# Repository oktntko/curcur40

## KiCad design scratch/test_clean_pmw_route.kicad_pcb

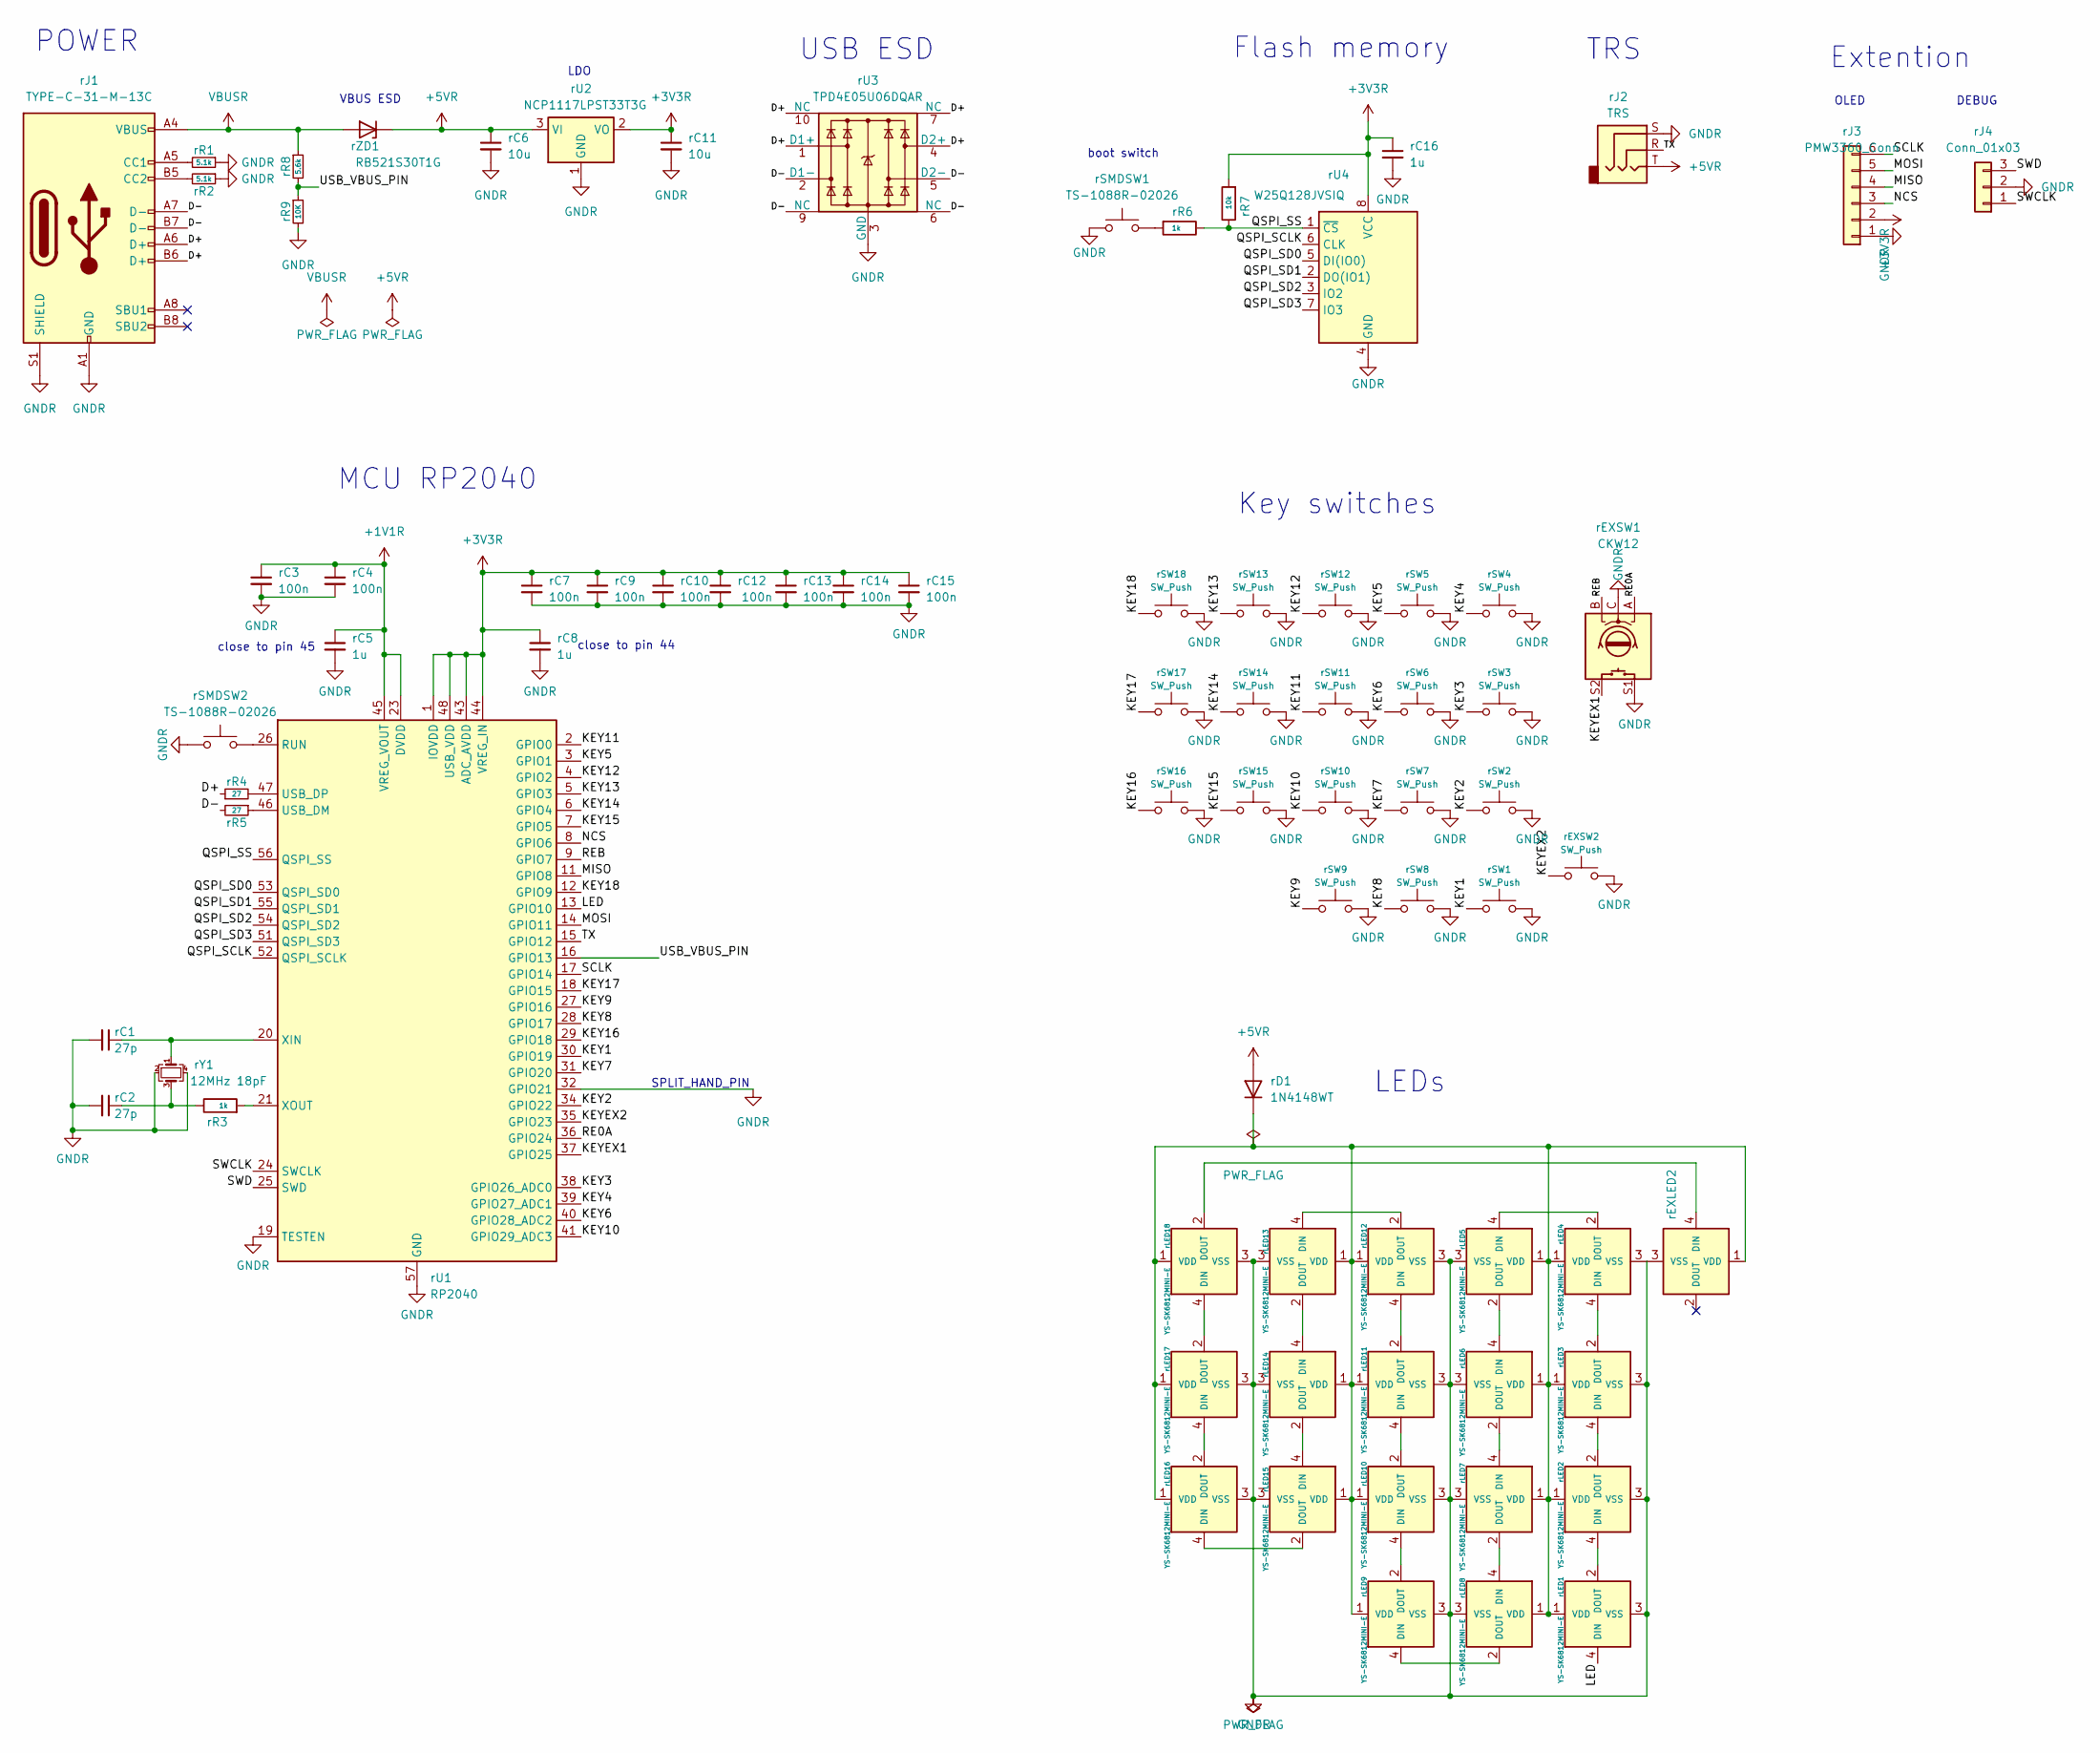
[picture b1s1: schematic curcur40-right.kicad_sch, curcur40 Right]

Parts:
rC1, rC2: 27p; C_0402_1005Metric
rC3, rC4, rC7, rC9, rC10, rC12, rC13, rC14, rC15: 100n; C_0402_1005Metric
rC5, rC8, rC16: 1u; C_0402_1005Metric
rC6, rC11: 10u; C_0402_1005Metric
rD1: 1N4148WT; D_SOD-523; JLCPCB Part # C232841
rEXLED2: YS-SK6812MINI-E
rEXSW1: CKW12
rEXSW2: SW_Push; keyswitch_choc12_hotswap_1u
rJ1: TYPE-C-31-M-13C; JLCPCB Part # C2848620
rJ2: TRS; PJ-398A-5A_PJ-399B-6A; JLCPCB Part # C128994
rJ3: PMW3360_Conn; PinHeader_1x06_P2.54mm_Vertical
rJ4: Conn_01x03; PinHeader_1x03_P2.54mm_Vertical
rLED1, rLED2, rLED3, rLED4, rLED5, rLED6, rLED7, rLED8, rLED9, rLED10, rLED11, rLED12, rLED13, rLED14, rLED15, rLED16, rLED17, rLED18: YS-SK6812MINI-E
rR1, rR2: 5.1k; R_0402_1005Metric
rR3, rR6: 1k; R_0402_1005Metric
rR4, rR5: 27; R_0402_1005Metric
rR7: 10k; R_0402_1005Metric
rR8: 5.6k; R_0402_1005Metric
rR9: 10K; R_0402_1005Metric
rSMDSW1, rSMDSW2: TS-1088R-02026; JLCPCB Part # C455280
rSW1, rSW2, rSW3, rSW4, rSW5, rSW6, rSW7, rSW8, rSW9, rSW10, rSW11, rSW12, rSW13, rSW14, rSW15, rSW16, rSW17, rSW18: SW_Push; keyswitch_choc12_hotswap_1u
rU1: RP2040; QFN-56-1EP_7x7mm_P0.4mm_EP3.2x3.2mm; JLCPCB Part # C2040
rU2: NCP1117LPST33T3G; SOT-223-3_TabPin2; JLCPCB Part # C146799
rU3: TPD4E05U06DQAR; USON-10_2.5x1.0mm_P0.5mm; JLCPCB Part # C138714
rU4: W25Q128JVSIQ; SOIC-8_5.3x5.3mm_P1.27mm; JLCPCB Part # C113767
rY1: 12MHz 18pF; Crystal_SMD_3225-4Pin_3.2x2.5mm; MFR.Part # Q22FA23V0041800; JLCPCB Part # C91749
rZD1: RB521S30T1G; D_SOD-523; JLCPCB Part # C145179

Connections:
+1V1R: rC3.1, rC4.1, rC5.1, rU1.23 (DVDD), rU1.45 (VREG_VOUT), rU1.50 (DVDD)
+3V3R: rC7.1, rC8.1, rC9.1, rC10.1, rC11.1, rC12.1, rC13.1, rC14.1, rC15.1, rC16.1, rJ3.2, rR7.2, rU1.1 (IOVDD), rU1.10 (IOVDD), rU1.22 (IOVDD), rU1.33 (IOVDD), rU1.42 (IOVDD), rU1.43 (ADC_AVDD), rU1.44 (VREG_IN), rU1.48 (USB_VDD), rU1.49 (IOVDD), rU2.2 (VO), rU4.8 (VCC); also elsewhere on the board
+5VR: rC6.1, rD1.2 (A), rJ2.T, rU2.3 (VI), rZD1.1 (K)
/D+: rJ1.A6 (D+), rJ1.B6 (D+), rR4.1, rU3.1 (D1+), rU3.4 (D2+), rU3.7 (NC), rU3.10 (NC)
/D-: rJ1.A7 (D-), rJ1.B7 (D-), rR5.2, rU3.2 (D1-), rU3.5 (D2-), rU3.6 (NC), rU3.9 (NC)
/KEY1: rSW1.1, rU1.30 (GPIO19)
/KEY2: rSW2.1, rU1.34 (GPIO22)
/KEY3: rSW3.1, rU1.38 (GPIO26_ADC0)
/KEY4: rSW4.1, rU1.39 (GPIO27_ADC1)
/KEY5: rSW5.1, rU1.3 (GPIO1)
/KEY6: rSW6.1, rU1.40 (GPIO28_ADC2)
/KEY7: rSW7.1, rU1.31 (GPIO20)
/KEY8: rSW8.1, rU1.28 (GPIO17)
/KEY9: rSW9.1, rU1.27 (GPIO16)
/KEY10: rSW10.1, rU1.41 (GPIO29_ADC3)
/KEY11: rSW11.1, rU1.2 (GPIO0)
/KEY12: rSW12.1, rU1.4 (GPIO2)
/KEY13: rSW13.1, rU1.5 (GPIO3)
/KEY14: rSW14.1, rU1.6 (GPIO4)
/KEY15: rSW15.1, rU1.7 (GPIO5)
/KEY16: rSW16.1, rU1.29 (GPIO18)
/KEY17: rSW17.1, rU1.18 (GPIO15)
/KEY18: rSW18.1, rU1.12 (GPIO9)
/KEYEX1: rEXSW1.S2, rU1.37 (GPIO25)
/KEYEX2: rEXSW2.1, rU1.35 (GPIO23)
/LED: rLED1.4 (DIN), rU1.13 (GPIO10)
/MISO: rJ3.4, rU1.11 (GPIO8); also elsewhere on the board
/MOSI: rJ3.5, rU1.14 (GPIO11); also elsewhere on the board
/NCS: rJ3.3, rU1.8 (GPIO6); also elsewhere on the board
/QSPI_SCLK: rU1.52 (QSPI_SCLK), rU4.6 (CLK)
/QSPI_SD0: rU1.53 (QSPI_SD0), rU4.5 (DI(IO0))
/QSPI_SD1: rU1.55 (QSPI_SD1), rU4.2 (DO(IO1))
/QSPI_SD2: rU1.54 (QSPI_SD2), rU4.3 (IO2)
/QSPI_SD3: rU1.51 (QSPI_SD3), rU4.7 (IO3)
/QSPI_SS: rR6.1, rR7.1, rU1.56 (QSPI_SS), rU4.1 (~CS)
/RE0A: rEXSW1.A, rU1.36 (GPIO24)
/REB: rEXSW1.B, rU1.9 (GPIO7)
/SCLK: rJ3.6, rU1.17 (GPIO14); also elsewhere on the board
/SWCLK: rJ4.1, rU1.24 (SWCLK)
/SWD: rJ4.3, rU1.25 (SWD)
/TX: rJ2.R, rU1.15 (GPIO12)
/USB_VBUS_PIN: rR8.2, rR9.1, rU1.16 (GPIO13)
GNDR: rC1.2, rC2.2, rC3.2, rC4.2, rC5.2, rC6.2, rC7.2, rC8.2, rC9.2, rC10.2, rC11.2, rC12.2, rC13.2, rC14.2, rC15.2, rC16.2, rEXLED2.3 (VSS), rEXSW1.C, rEXSW1.S1, rEXSW2.2, rJ1.A1 (GND), rJ1.A12 (GND), rJ1.B1 (GND), rJ1.B12 (GND), rJ1.S1 (SHIELD), rJ2.S, rJ3.1, rJ4.2, rLED1.3 (VSS), rLED2.3 (VSS), rLED3.3 (VSS), rLED4.3 (VSS), rLED5.3 (VSS), rLED6.3 (VSS), rLED7.3 (VSS), rLED8.3 (VSS), rLED9.3 (VSS), rLED10.3 (VSS), rLED11.3 (VSS), rLED12.3 (VSS), rLED13.3 (VSS), rLED14.3 (VSS), rLED15.3 (VSS), rLED16.3 (VSS), rLED17.3 (VSS), rLED18.3 (VSS), rR1.1, rR2.1, rR9.2, rSMDSW1.1, rSMDSW2.1, rSW1.2, rSW2.2, rSW3.2, rSW4.2, rSW5.2, rSW6.2, rSW7.2, rSW8.2, rSW9.2, rSW10.2, rSW11.2, rSW12.2, rSW13.2, rSW14.2, rSW15.2, rSW16.2, rSW17.2, rSW18.2, rU1.19 (TESTEN), rU1.32 (GPIO21), rU1.57 (GND), rU2.1 (GND), rU3.3 (GND), rU3.8 (GND), rU4.4 (GND), rY1.2, rY1.4; also elsewhere on the board
unnamed: rC2.1, rR3.1, rY1.3
unnamed: rD1.1 (K), rEXLED2.1 (VDD), rLED1.1 (VDD), rLED2.1 (VDD), rLED3.1 (VDD), rLED4.1 (VDD), rLED5.1 (VDD), rLED6.1 (VDD), rLED7.1 (VDD), rLED8.1 (VDD), rLED9.1 (VDD), rLED10.1 (VDD), rLED11.1 (VDD), rLED12.1 (VDD), rLED13.1 (VDD), rLED14.1 (VDD), rLED15.1 (VDD), rLED16.1 (VDD), rLED17.1 (VDD), rLED18.1 (VDD)
unnamed: rEXLED2.4 (DIN), rLED18.2 (DOUT)
unnamed: rJ1.A5 (CC1), rR1.2
unnamed: rJ1.B5 (CC2), rR2.2
unnamed: rLED1.2 (DOUT), rLED2.4 (DIN)
unnamed: rLED2.2 (DOUT), rLED3.4 (DIN)
unnamed: rLED3.2 (DOUT), rLED4.4 (DIN)
unnamed: rLED4.2 (DOUT), rLED5.4 (DIN)
unnamed: rLED5.2 (DOUT), rLED6.4 (DIN)
unnamed: rLED6.2 (DOUT), rLED7.4 (DIN)
unnamed: rLED7.2 (DOUT), rLED8.4 (DIN)
unnamed: rLED8.2 (DOUT), rLED9.4 (DIN)
unnamed: rLED9.2 (DOUT), rLED10.4 (DIN)
unnamed: rLED10.2 (DOUT), rLED11.4 (DIN)
unnamed: rLED11.2 (DOUT), rLED12.4 (DIN)
unnamed: rLED12.2 (DOUT), rLED13.4 (DIN)
unnamed: rLED13.2 (DOUT), rLED14.4 (DIN)
unnamed: rLED14.2 (DOUT), rLED15.4 (DIN)
unnamed: rLED15.2 (DOUT), rLED16.4 (DIN)
unnamed: rLED16.2 (DOUT), rLED17.4 (DIN)
unnamed: rLED17.2 (DOUT), rLED18.4 (DIN)
unnamed: rR6.2, rSMDSW1.2
unnamed: rSMDSW2.2, rU1.26 (RUN)
unnamed: rR5.1, rU1.46 (USB_DM)
unnamed: rR4.2, rU1.47 (USB_DP)
unnamed: rC1.1, rU1.20 (XIN), rY1.1
unnamed: rR3.2, rU1.21 (XOUT)
VBUSR: rJ1.A4 (VBUS), rJ1.A9 (VBUS), rJ1.B4 (VBUS), rJ1.B9 (VBUS), rR8.1, rZD1.2 (A)

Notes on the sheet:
USB ESD
TRS
Flash memory
MCU RP2040
DEBUG
POWER
boot switch
LDO
Key switches
LEDs
Extention
VBUS ESD
OLED
close to pin 45
close to pin 44
SPLIT_HAND_PIN

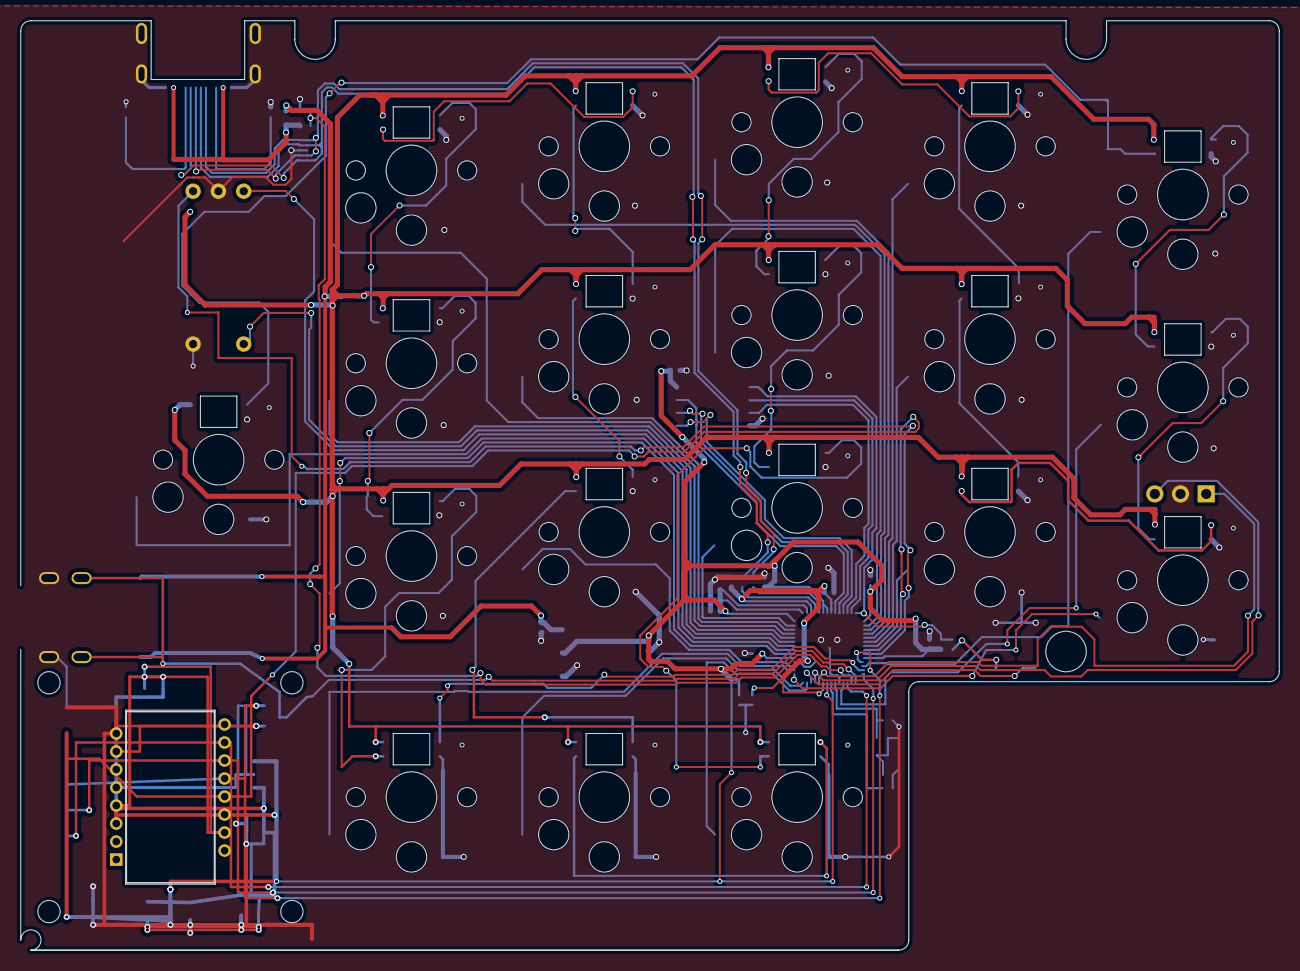
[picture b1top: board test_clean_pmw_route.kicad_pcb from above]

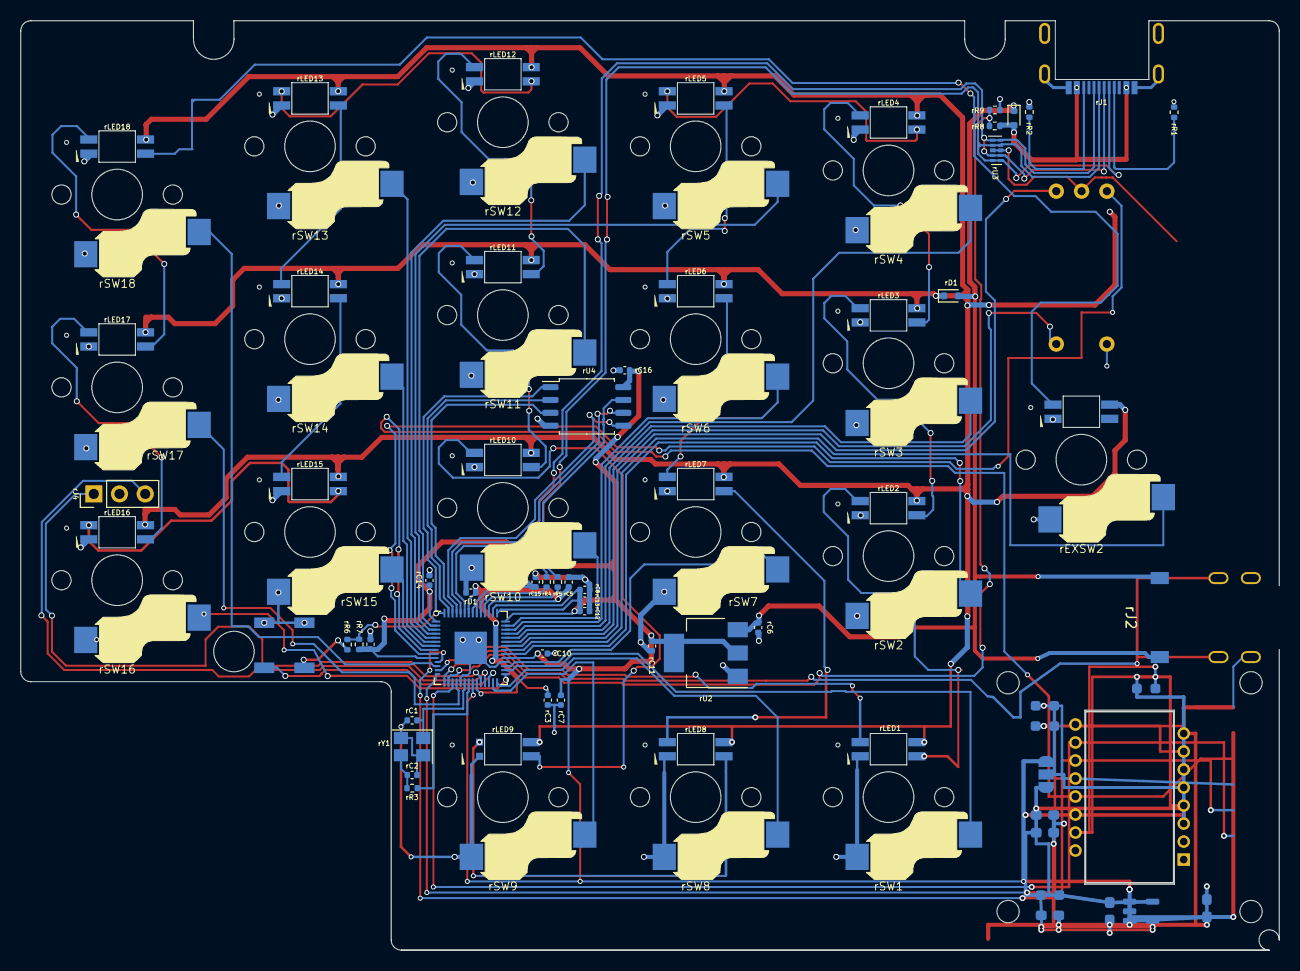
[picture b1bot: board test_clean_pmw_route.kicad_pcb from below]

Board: 2 copper layers, 124.3 x 91.8 mm, 88 parts (87 on the bottom side), 77 nets.

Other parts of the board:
C1: 4.7uF/10V; C_0603_1608Metric_Pad1.08x0.95mm_HandSolder
C2: 100nF; C_0603_1608Metric_Pad1.08x0.95mm_HandSolder
C3, C4: 1uF; C_0603_1608Metric_Pad1.08x0.95mm_HandSolder
C5: 22nF; C_0603_1608Metric_Pad1.08x0.95mm_HandSolder
JP1: SolderJumper_3_Open; SolderJumper-3_P1.3mm_Open_RoundedPad1.0x1.5mm_NumberLabels
R1, R2: 10k; R_0603_1608Metric_Pad0.98x0.95mm_HandSolder
R3: 39R; R_0603_1608Metric_Pad0.98x0.95mm_HandSolder
R4: 28k; R_0603_1608Metric_Pad0.98x0.95mm_HandSolder
U1: PMW3360DM-T2QU; PMW3360DM-T2QU_16Pin
U2: TLV74318PDBVR; SOT-23-5

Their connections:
+1V8_PMW: C1.1, C2.1, C4.1, JP1.3 (B), R3.1, R4.1, U1.3 (VDDPIX), U1.4 (VDD), U2.5 (OUT)
+3V3R: C3.1, JP1.1 (A), U2.1 (IN), U2.3 (EN); also elsewhere on the board
/MISO: R2.2, U1.12 (MISO); also elsewhere on the board
/MOSI: U1.11 (MOSI); also elsewhere on the board
/NCS: U1.13 (~CS); also elsewhere on the board
/RESET: R1.2, U1.7 (~RESET)
/SCLK: U1.10 (SCLK); also elsewhere on the board
GNDR: C1.2, C2.2, C3.2, C4.2, C5.2, U1.8 (GND), U2.2 (GND); also elsewhere on the board
unnamed: R3.2, U1.15 (LED_P)
unnamed: C5.1, R4.2, U2.4 (NC)
V_{IO}: JP1.2 (C), R1.1, R2.1, U1.5 (VDDIO)

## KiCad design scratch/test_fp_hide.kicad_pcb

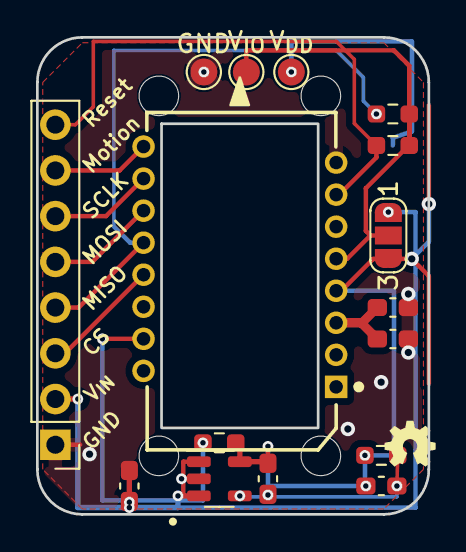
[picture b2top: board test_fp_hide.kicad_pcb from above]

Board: 2 copper layers, 21.8 x 26.5 mm, 20 parts (0 on the bottom side), 13 nets.

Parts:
C1: 4.7uF/10V; C_0603_1608Metric_Pad1.08x0.95mm_HandSolder
C2: 100nF; C_0603_1608Metric_Pad1.08x0.95mm_HandSolder
C3, C4: 1uF; C_0603_1608Metric_Pad1.08x0.95mm_HandSolder
C5: 22nF; C_0603_1608Metric_Pad1.08x0.95mm_HandSolder
H1, H2, H3, H4: MountingHole_2.2mm_M2
J1: Conn_01x08; PinHeader_1x08_P2.54mm_Vertical
JP1: SolderJumper_3_Open; SolderJumper-3_P1.3mm_Open_RoundedPad1.0x1.5mm_NumberLabels
R1, R2: 10k; R_0603_1608Metric_Pad0.98x0.95mm_HandSolder
R3: 39R; R_0603_1608Metric_Pad0.98x0.95mm_HandSolder
R4: 28k; R_0603_1608Metric_Pad0.98x0.95mm_HandSolder
TP1: VIO; TestPoint_Pad_D1.5mm
TP2: VDD; TestPoint_Pad_D1.5mm
TP3: GND; TestPoint_Pad_D1.5mm
U1: PMW3360DM-T2QU; PMW3360DM-T2QU_16Pin
U2: TLV74318PDBVR; SOT-23-5

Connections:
/CS: J1.3, U1.13 (~CS)
/MISO: J1.4, R2.2, U1.12 (MISO)
/MOSI: J1.5, U1.11 (MOSI)
/MOTION: J1.7, U1.9 (MOTION)
/RESET: J1.8, R1.2, U1.7 (~RESET)
/SCLK: J1.6, U1.10 (SCLK)
GND: C1.2, C2.2, C3.2, C4.2, C5.2, J1.1, TP3.1, U1.8 (GND), U2.2 (GND)
unnamed: R3.2, U1.15 (LED_P)
unnamed: C1.1, C2.1, U1.3 (VDDPIX)
unnamed: C5.1, R4.2, U2.4 (NC)
VDD: C4.1, JP1.3 (B), R3.1, R4.1, TP2.1, U1.4 (VDD), U2.5 (OUT)
V_{IN}: C3.1, J1.2, JP1.1 (A), U2.1 (IN), U2.3 (EN)
V_{IO}: JP1.2 (C), R1.1, R2.1, TP1.1, U1.5 (VDDIO)

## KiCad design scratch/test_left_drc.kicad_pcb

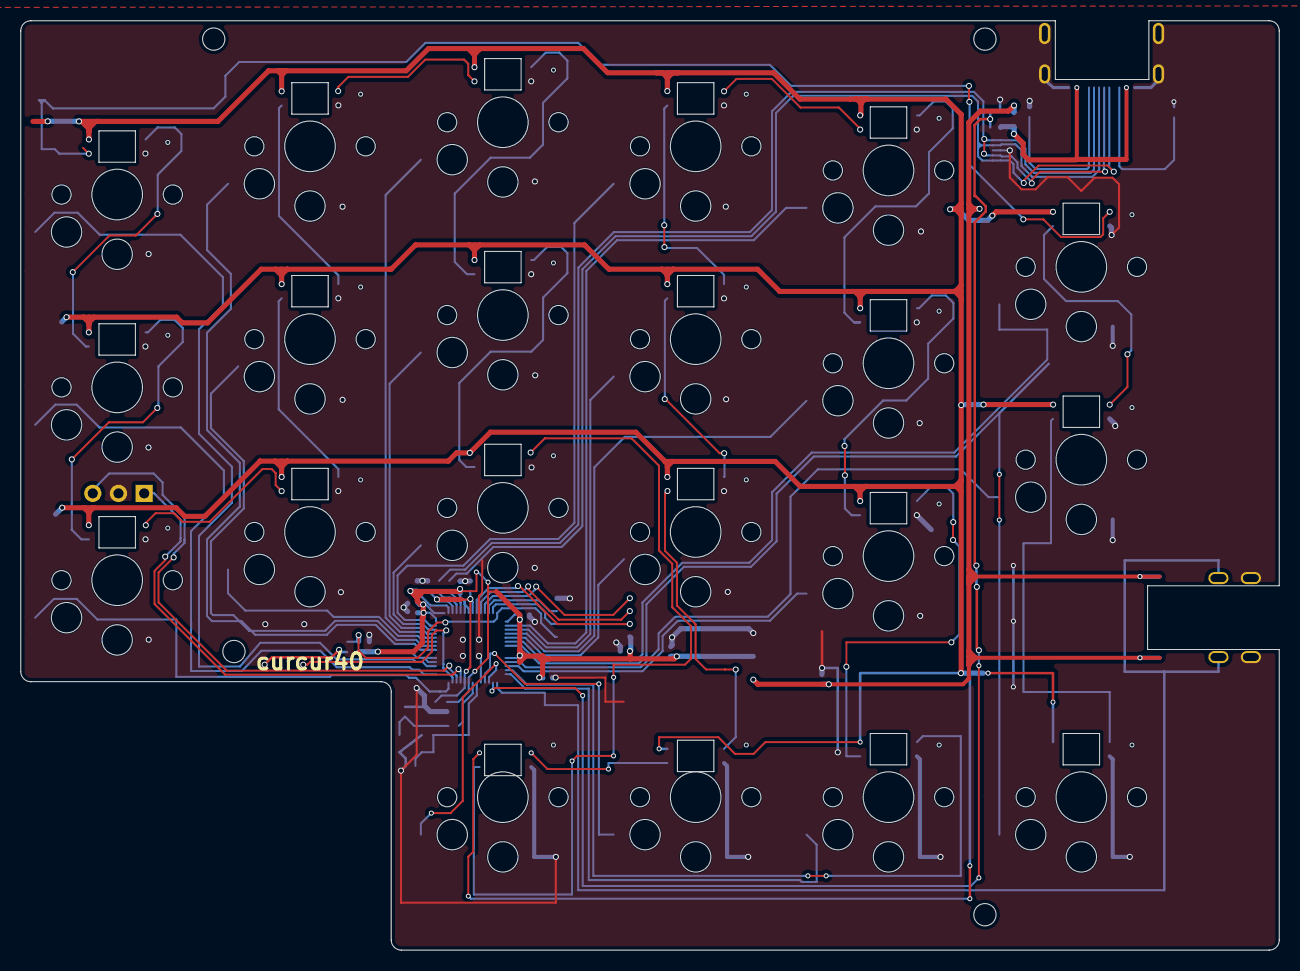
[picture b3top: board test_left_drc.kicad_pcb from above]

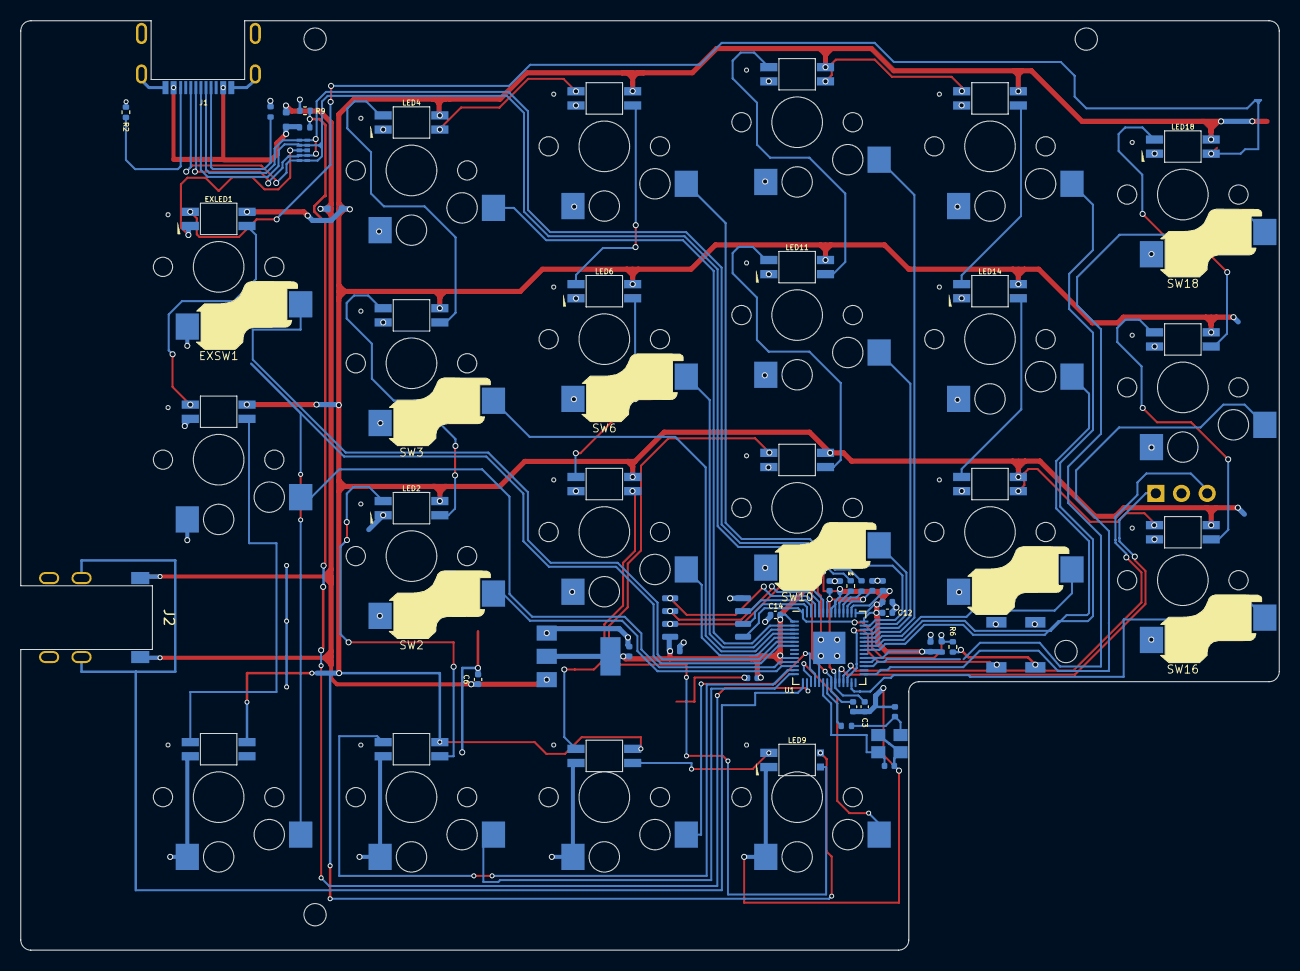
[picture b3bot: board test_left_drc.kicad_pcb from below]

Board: 2 copper layers, 124.3 x 91.8 mm, 79 parts (79 on the bottom side), 69 nets.

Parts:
C1, C2: 27p; C_0402_1005Metric
C3, C4, C7, C9, C10, C12, C13, C14, C15: 100n; C_0402_1005Metric
C5, C8, C16: 1u; C_0402_1005Metric
C6, C11: 10u; C_0402_1005Metric
D1: 1N4148WT; D_SOD-523
EXLED1, EXLED2, EXLED3: YS-SK6812MINI-E
EXSW1, EXSW2, EXSW3: SW_Push; keyswitch_choc12_hotswap_1u
J1: TYPE-C-31-M-13C
J2: TRS; PJ-398A-5A_PJ-399B-6A
J4: Conn_01x03; PinHeader_1x03_P2.54mm_Vertical
LED1, LED2, LED3, LED4, LED5, LED6, LED7, LED8, LED9, LED10, LED11, LED12, LED13, LED14, LED15, LED16, LED17, LED18: YS-SK6812MINI-E
R1, R2: 5.1k; R_0402_1005Metric
R3, R6: 1k; R_0402_1005Metric
R4, R5: 27; R_0402_1005Metric
R7: 10k; R_0402_1005Metric
R8: 5.6k; R_0402_1005Metric
R9: 10K; R_0402_1005Metric
SMDSW1, SMDSW2: TS-1088R-02026
SW1, SW2, SW3, SW4, SW5, SW6, SW7, SW8, SW9, SW10, SW11, SW12, SW13, SW14, SW15, SW16, SW17, SW18: SW_Push; keyswitch_choc12_hotswap_1u
U1: RP2040; QFN-56-1EP_7x7mm_P0.4mm_EP3.2x3.2mm
U2: NCP1117LPST33T3G; SOT-223-3_TabPin2
U3: TPD4E05U06DQAR; USON-10_2.5x1.0mm_P0.5mm
U4: W25Q128JVSIQ; SOIC-8_5.23x5.23mm_P1.27mm
Y1: 12MHz 18pF; Crystal_SMD_3225-4Pin_3.2x2.5mm
ZD1: RB521S30T1G; D_SOD-523

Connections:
+1V1: C3.1, C4.1, C5.1, U1.23 (DVDD), U1.45 (VREG_VOUT), U1.50 (DVDD)
+3V3: C7.1, C8.1, C9.1, C10.1, C11.1, C12.1, C13.1, C14.1, C15.1, C16.1, R7.2, U1.1 (IOVDD), U1.10 (IOVDD), U1.22 (IOVDD), U1.32 (GPIO21), U1.33 (IOVDD), U1.42 (IOVDD), U1.43 (ADC_AVDD), U1.44 (VREG_IN), U1.48 (USB_VDD), U1.49 (IOVDD), U2.2 (VO), U4.8 (VCC)
+5V: C6.1, D1.2 (A), J2.T, U2.3 (VI), ZD1.1 (K)
/D+: J1.A6 (D+), J1.B6 (D+), R4.1, U3.1 (D1+), U3.4 (D2+), U3.7 (NC), U3.10 (NC)
/D-: J1.A7 (D-), J1.B7 (D-), R5.2, U3.2 (D1-), U3.5 (D2-), U3.6 (NC), U3.9 (NC)
/KEY1: SW1.1, U1.14 (GPIO11)
/KEY2: SW2.1, U1.12 (GPIO9)
/KEY3: SW3.1, U1.4 (GPIO2)
/KEY4: SW4.1, U1.2 (GPIO0)
/KEY5: SW5.1, U1.41 (GPIO29_ADC3)
/KEY6: SW6.1, U1.3 (GPIO1)
/KEY7: SW7.1, U1.5 (GPIO3)
/KEY8: SW8.1, U1.18 (GPIO15)
/KEY9: SW9.1, U1.17 (GPIO14)
/KEY10: SW10.1, U1.40 (GPIO28_ADC2)
/KEY11: SW11.1, U1.39 (GPIO27_ADC1)
/KEY12: SW12.1, U1.38 (GPIO26_ADC0)
/KEY13: SW13.1, U1.35 (GPIO23)
/KEY14: SW14.1, U1.36 (GPIO24)
/KEY15: SW15.1, U1.37 (GPIO25)
/KEY16: SW16.1, U1.27 (GPIO16)
/KEY17: SW17.1, U1.29 (GPIO18)
/KEY18: SW18.1, U1.31 (GPIO20)
/KEYEX1: EXSW1.1, U1.6 (GPIO4)
/KEYEX2: EXSW2.1, U1.11 (GPIO8)
/KEYEX3: EXSW3.1, U1.7 (GPIO5)
/LED: LED1.4 (DIN), U1.13 (GPIO10)
/QSPI_SCLK: U1.52 (QSPI_SCLK), U4.6 (CLK)
/QSPI_SD0: U1.53 (QSPI_SD0), U4.5 (DI(IO0))
/QSPI_SD1: U1.55 (QSPI_SD1), U4.2 (DO(IO1))
/QSPI_SD2: U1.54 (QSPI_SD2), U4.3 (IO2)
/QSPI_SD3: U1.51 (QSPI_SD3), U4.7 (IO3)
/QSPI_SS: R6.1, R7.1, U1.56 (QSPI_SS), U4.1 (~CS)
/SWCLK: J4.1, U1.24 (SWCLK)
/SWD: J4.3, U1.25 (SWD)
/TX: J2.R, U1.15 (GPIO12)
/USB_VBUS_PIN: R8.2, R9.1, U1.16 (GPIO13)
GND: C1.2, C2.2, C3.2, C4.2, C5.2, C6.2, C7.2, C8.2, C9.2, C10.2, C11.2, C12.2, C13.2, C14.2, C15.2, C16.2, EXLED1.3 (VSS), EXLED2.3 (VSS), EXLED3.3 (VSS), EXSW1.2, EXSW2.2, EXSW3.2, J1.A1 (GND), J1.A12 (GND), J1.B1 (GND), J1.B12 (GND), J1.S1 (SHIELD), J2.S, J4.2, LED1.3 (VSS), LED2.3 (VSS), LED3.3 (VSS), LED4.3 (VSS), LED5.3 (VSS), LED6.3 (VSS), LED7.3 (VSS), LED8.3 (VSS), LED9.3 (VSS), LED10.3 (VSS), LED11.3 (VSS), LED12.3 (VSS), LED13.3 (VSS), LED14.3 (VSS), LED15.3 (VSS), LED16.3 (VSS), LED17.3 (VSS), LED18.3 (VSS), R1.1, R2.1, R9.2, SMDSW1.1, SMDSW2.1, SW1.2, SW2.2, SW3.2, SW4.2, SW5.2, SW6.2, SW7.2, SW8.2, SW9.2, SW10.2, SW11.2, SW12.2, SW13.2, SW14.2, SW15.2, SW16.2, SW17.2, SW18.2, U1.19 (TESTEN), U1.57 (GND), U2.1 (GND), U3.3 (GND), U3.8 (GND), U4.4 (GND), Y1.2, Y1.4
unnamed: C2.1, R3.1, Y1.3
unnamed: D1.1 (K), EXLED1.1 (VDD), EXLED2.1 (VDD), EXLED3.1 (VDD), LED1.1 (VDD), LED2.1 (VDD), LED3.1 (VDD), LED4.1 (VDD), LED5.1 (VDD), LED6.1 (VDD), LED7.1 (VDD), LED8.1 (VDD), LED9.1 (VDD), LED10.1 (VDD), LED11.1 (VDD), LED12.1 (VDD), LED13.1 (VDD), LED14.1 (VDD), LED15.1 (VDD), LED16.1 (VDD), LED17.1 (VDD), LED18.1 (VDD)
unnamed: EXLED1.4 (DIN), LED18.2 (DOUT)
unnamed: EXLED1.2 (DOUT), EXLED2.4 (DIN)
unnamed: EXLED2.2 (DOUT), EXLED3.4 (DIN)
unnamed: J1.A5 (CC1), R1.2
unnamed: J1.B5 (CC2), R2.2
unnamed: LED1.2 (DOUT), LED2.4 (DIN)
unnamed: LED2.2 (DOUT), LED3.4 (DIN)
unnamed: LED3.2 (DOUT), LED4.4 (DIN)
unnamed: LED4.2 (DOUT), LED5.4 (DIN)
unnamed: LED5.2 (DOUT), LED6.4 (DIN)
unnamed: LED6.2 (DOUT), LED7.4 (DIN)
unnamed: LED7.2 (DOUT), LED8.4 (DIN)
unnamed: LED8.2 (DOUT), LED9.4 (DIN)
unnamed: LED9.2 (DOUT), LED10.4 (DIN)
unnamed: LED10.2 (DOUT), LED11.4 (DIN)
unnamed: LED11.2 (DOUT), LED12.4 (DIN)
unnamed: LED12.2 (DOUT), LED13.4 (DIN)
unnamed: LED13.2 (DOUT), LED14.4 (DIN)
unnamed: LED14.2 (DOUT), LED15.4 (DIN)
unnamed: LED15.2 (DOUT), LED16.4 (DIN)
unnamed: LED16.2 (DOUT), LED17.4 (DIN)
unnamed: LED17.2 (DOUT), LED18.4 (DIN)
unnamed: R6.2, SMDSW1.2
unnamed: SMDSW2.2, U1.26 (RUN)
unnamed: R5.1, U1.46 (USB_DM)
unnamed: R4.2, U1.47 (USB_DP)
unnamed: C1.1, U1.20 (XIN), Y1.1
unnamed: R3.2, U1.21 (XOUT)
VBUS: J1.A4 (VBUS), J1.A9 (VBUS), J1.B4 (VBUS), J1.B9 (VBUS), R8.1, ZD1.2 (A)

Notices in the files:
scratch/test_fp_hide.kicad_pcb:
Open Source Hardware, CERN-OHL-P v2
